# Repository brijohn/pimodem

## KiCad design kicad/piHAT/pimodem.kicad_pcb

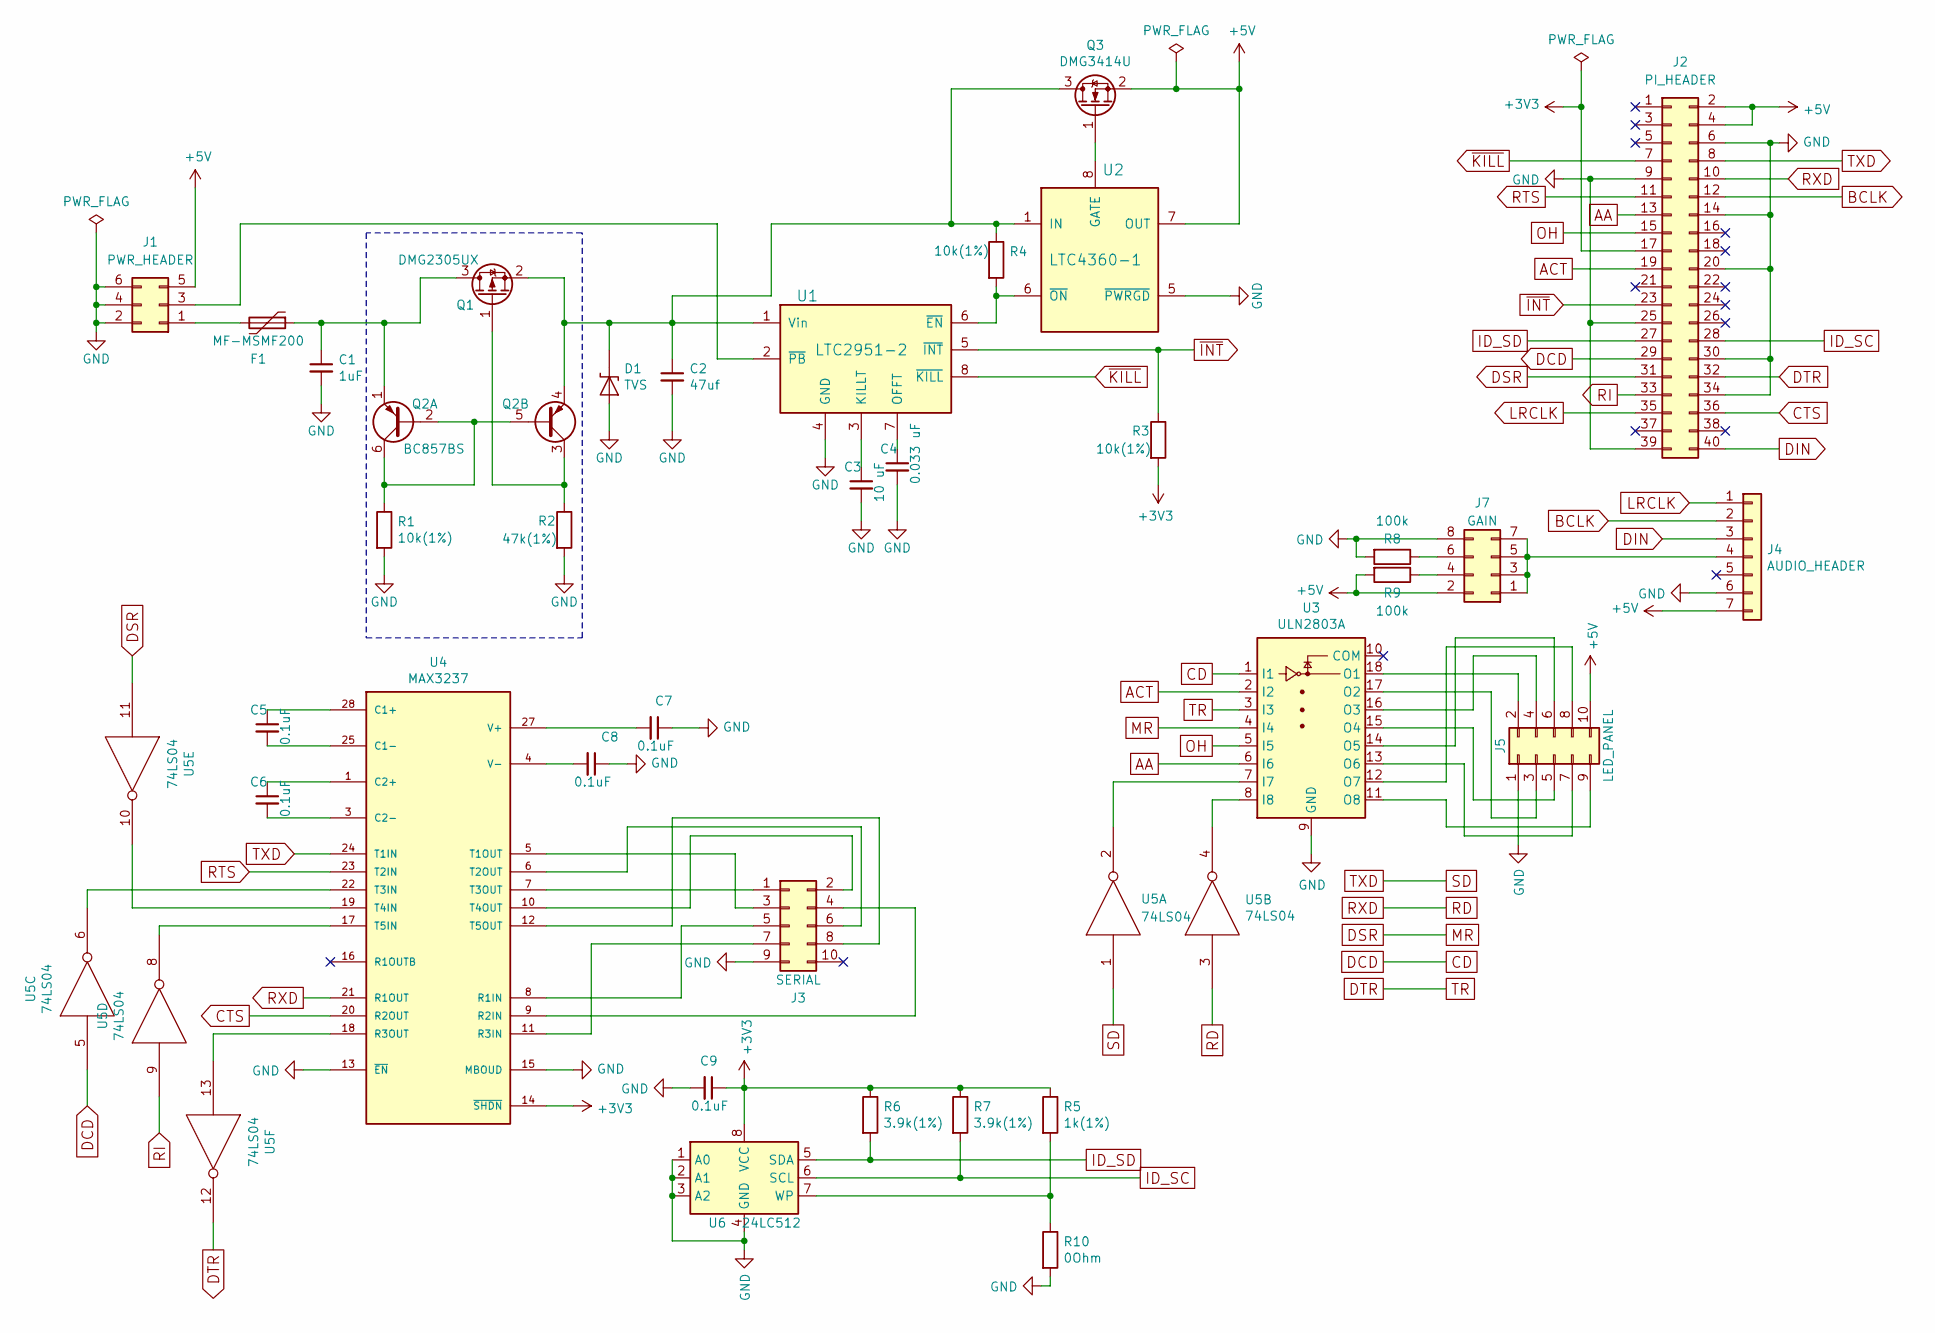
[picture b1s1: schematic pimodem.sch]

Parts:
C1: 1uF; C_0805_2012Metric; Digikey 478-1405-1-ND
C2: 47uf; C_0805_2012Metric; Digikey 445-8239-1-ND
C3: 10 uF; C_0805_2012Metric; Digikey 399-4925-1-ND
C4: 0.033 uF; C_0805_2012Metric; Digikey 732-8024-1-ND
C5: 0.1uF; C_0805_2012Metric; Digikey 399-7999-1-ND
C6, C7, C8, C9: 0.1uF; C_0805_2012Metric
D1: TVS; D_SMB; Digikey SMBJ5.0ALFCT-ND
F1: MF-MSMF200; R_1812_4532Metric; Digikey MF-MSMF200-2CT-ND
J1: PWR_HEADER; Molex_Micro-Fit_3.0_43045-0612_2x03_P3.00mm_Vertical; Digikey WM10679-ND
J2: PI_HEADER; PinSocket_2x20_P2.54mm_Vertical; Digikey S9200-ND
J3: SERIAL; PinHeader_2x05_P2.54mm_Vertical; Digikey 609-3243-ND
J4: AUDIO_HEADER; MAX98357_I2S_DAC; Digikey A31117-ND
J5: LED_PANEL; PinHeader_2x05_P2.54mm_Vertical; Digikey 609-3243-ND
J7: GAIN; PinHeader_2x04_P2.54mm_Vertical; Digikey 609-3391-ND
Q1: DMG2305UX; SOT-23; Digikey DMG2305UX-13DICT-ND
Q2: BC857BS; SOT-363_SC-70-6; Digikey BC857BS-7FDICT-ND
Q3: DMG3414U; SOT-23; Digikey DMG3414U-7DICT-ND
R1: 10k(1%); R_0805_2012Metric; Digikey 311-10.0KCRCT-ND
R2: 47k(1%); R_0805_2012Metric; Digikey 311-47.0KCRCT-ND
R3, R4: 10k(1%); R_0805_2012Metric
R5: 1k(1%); R_0805_2012Metric; Digikey 311-1.00KCRCT-ND
R6: 3.9k(1%); R_0805_2012Metric; Digikey RMCF0805FT3K90CT-ND
R7: 3.9k(1%); R_0805_2012Metric
R8: 100k; R_0805_2012Metric; Digikey 311-100KCRCT-ND
R9: 100k; R_0805_2012Metric
R10: 0Ohm; R_0805_2012Metric; Digikey 311-0.0ARCT-ND
U1: LTC2951-2; SOT-23-8; Digikey LTC2951CTS8-2#TRMPBFCT-ND
U2: LTC4360-1; SC-70-8; Digikey LTC4360ISC8-1#TRMPBFCT-ND
U3: ULN2803A; SOIC-18W_7.5x11.6mm_P1.27mm; Digikey 296-15777-1-ND
U4: MAX3237; SSOP-28_5.3x10.2mm_P0.65mm; Digikey MAX3237EAI+-ND
U5: 74LS04; SOIC-14_3.9x8.7mm_P1.27mm; Digikey 296-14875-1-ND
U6: 24LC512; SOIC-8_3.9x4.9mm_P1.27mm; Digikey CAT24C512WI-GT3OSCT-ND

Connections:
+3V3: C9.1, J2.17, R3.2, R5.1, R6.1, R7.1, U4.14 (~SHDN~), U4.26 (+3V3), U6.8 (VCC)
+5V: J1.5, J2.2, J2.4, J4.7, J5.10, J7.2, Q3.2 (S), R9.2, U2.7 (OUT), U5.14 (+5V)
AA: J2.13, U3.6 (I6)
ACT: J2.19, U3.2 (I2)
BCLK: J2.12, J4.2
CD: J2.29, U3.1 (I1), U5.5
CTS: J2.36, U4.20 (R2OUT)
DIN: J2.40, J4.3
DSR: J2.31, U3.4 (I4), U5.11
DTR: J2.32, U3.3 (I3), U5.12
GND: C1.2, C2.2, C3.2, C4.2, C7.1, C8.1, C9.2, D1.2 (A2), J1.2, J1.4, J1.6, J2.6, J2.9, J2.14, J2.20, J2.25, J2.30, J2.34, J2.39, J3.9, J4.6, J5.1, J7.8, R1.2, R2.2, R8.2, R10.2, U1.4 (GND), U2.2 (GND), U2.3 (GND), U2.4 (GND), U2.5 (~PWRGD~), U3.9 (GND), U4.2 (GND), U4.13 (~EN~), U4.15 (MBOUD), U5.7 (GND), U6.1 (A0), U6.2 (A1), U6.3 (A2), U6.4 (GND)
ID_SC: J2.28, R7.2, U6.6 (SCL)
ID_SD: J2.27, R6.2, U6.5 (SDA)
LRCLK: J2.35, J4.1
unnamed: C1.1, F1.1, Q1.3 (D), Q2.1 (E1)
unnamed: C2.1, D1.1 (A1), Q1.2 (S), Q2.4 (E2), Q3.3 (D), R4.1, U1.1 (Vin), U2.1 (IN)
unnamed: C3.1, U1.3 (KILLT)
unnamed: C4.1, U1.7 (OFFT)
unnamed: C5.1, U4.28 (C1+)
unnamed: C5.2, U4.25 (C1-)
unnamed: C6.1, U4.1 (C2+)
unnamed: C6.2, U4.3 (C2-)
unnamed: C7.2, U4.27 (V+)
unnamed: C8.2, U4.4 (V-)
unnamed: F1.2, J1.1
unnamed: J1.3, U1.2 (~PB~)
unnamed: J3.1, U4.7 (T3OUT)
unnamed: J3.2, U4.10 (T4OUT)
unnamed: J3.3, U4.5 (T1OUT)
unnamed: J3.4, U4.9 (R2IN)
unnamed: J3.5, U4.8 (R1IN)
unnamed: J3.6, U4.6 (T2OUT)
unnamed: J3.7, U4.11 (R3IN)
unnamed: J3.8, U4.12 (T5OUT)
unnamed: J4.4, J7.1, J7.3, J7.5, J7.7
unnamed: J5.2, U3.18 (O1)
unnamed: J5.3, U3.17 (O2)
unnamed: J5.4, U3.16 (O3)
unnamed: J5.5, U3.15 (O4)
unnamed: J5.6, U3.14 (O5)
unnamed: J5.7, U3.13 (O6)
unnamed: J5.8, U3.12 (O7)
unnamed: J5.9, U3.11 (O8)
unnamed: J7.4, R9.1
unnamed: J7.6, R8.1
unnamed: Q1.1 (G), Q2.3 (C2), R2.1
unnamed: Q2.2 (B1), Q2.5 (B2), Q2.6 (C1), R1.1
unnamed: Q3.1 (G), U2.8 (GATE)
unnamed: R4.2, U1.6 (~EN~), U2.6 (~ON~)
unnamed: R5.2, R10.1, U6.7 (WP)
unnamed: U3.7 (I7), U5.2
unnamed: U3.8 (I8), U5.4
unnamed: U4.17 (T5IN), U5.8
unnamed: U4.18 (R3OUT), U5.13
unnamed: U4.19 (T4IN), U5.10
unnamed: U4.22 (T3IN), U5.6
OH: J2.15, U3.5 (I5)
RD: J2.10, U4.21 (R1OUT), U5.3
RI: J2.33, U5.9
RTS: J2.11, U4.23 (T2IN)
SD: J2.8, U4.24 (T1IN), U5.1
~INT~: J2.23, R3.1, U1.5 (~INT~)
~KILL~: J2.7, U1.8 (~KILL~)

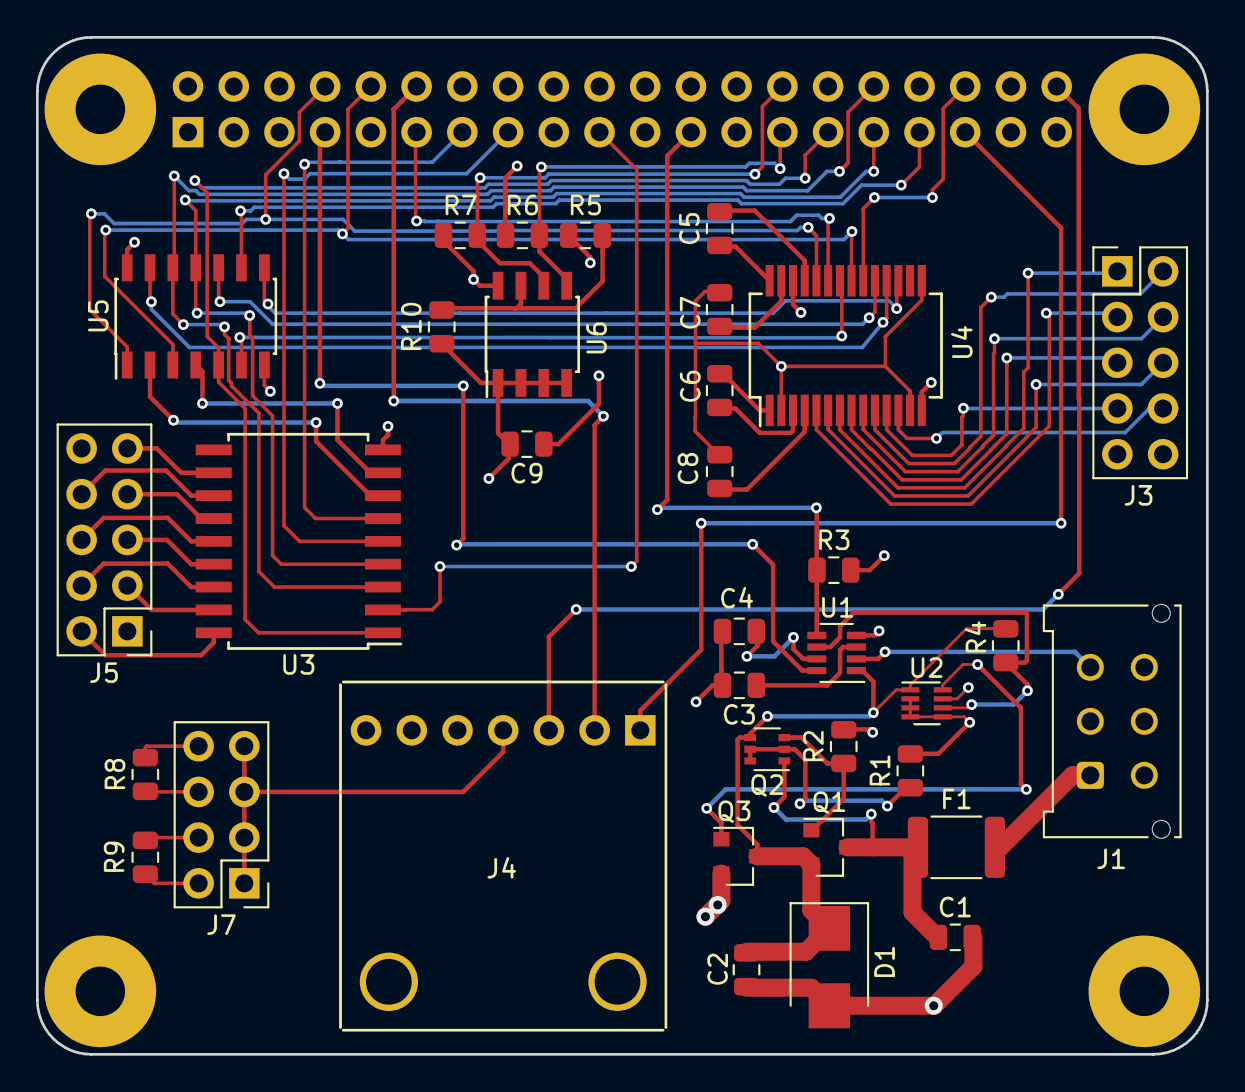
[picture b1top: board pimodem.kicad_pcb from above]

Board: 4 copper layers, 65.0 x 56.5 mm, 36 parts (1 on the bottom side), 63 nets.

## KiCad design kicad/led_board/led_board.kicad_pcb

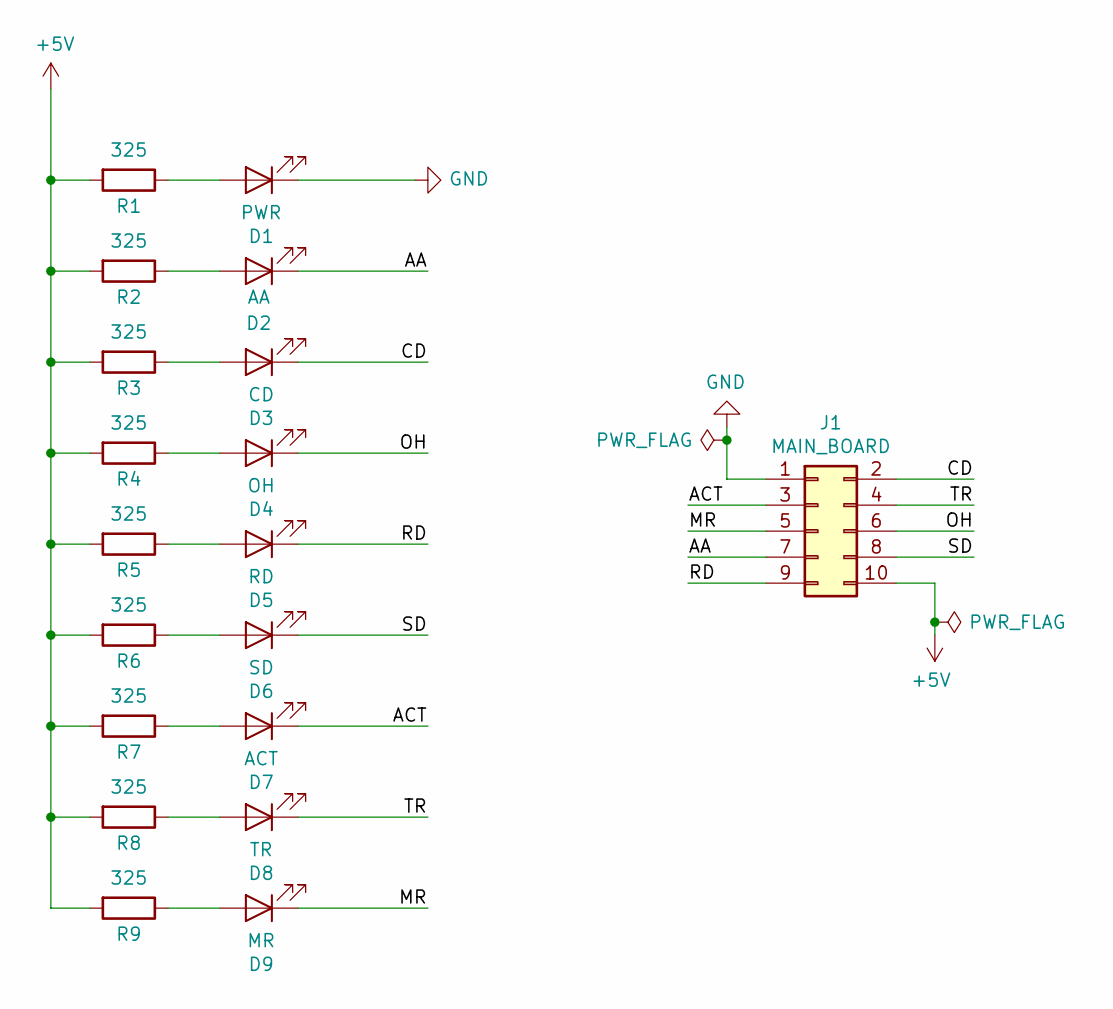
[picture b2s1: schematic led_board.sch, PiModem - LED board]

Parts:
D1: PWR; LED_D5.0mm
D2: AA; LED_D5.0mm
D3: CD; LED_D5.0mm
D4: OH; LED_D5.0mm
D5: RD; LED_D5.0mm
D6: SD; LED_D5.0mm
D7: ACT; LED_D5.0mm
D8: TR; LED_D5.0mm
D9: MR; LED_D5.0mm
J1: MAIN_BOARD; PinHeader_2x05_P2.54mm_Vertical
R1, R2, R3, R4, R5, R6, R7, R8, R9: 325; R_Axial_DIN0207_L6.3mm_D2.5mm_P10.16mm_Horizontal

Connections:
+5V: J1.10, R1.2, R2.2, R3.2, R4.2, R5.2, R6.2, R7.2, R8.2, R9.2
/AA: D2.1 (K), J1.7
/ACT: D7.1 (K), J1.3
/CD: D3.1 (K), J1.2
/MR: D9.1 (K), J1.5
/OH: D4.1 (K), J1.6
/RD: D5.1 (K), J1.9
/SD: D6.1 (K), J1.8
/TR: D8.1 (K), J1.4
GND: D1.1 (K), J1.1
unnamed: D1.2 (A), R1.1
unnamed: D2.2 (A), R2.1
unnamed: D3.2 (A), R3.1
unnamed: D4.2 (A), R4.1
unnamed: D5.2 (A), R5.1
unnamed: D6.2 (A), R6.1
unnamed: D7.2 (A), R7.1
unnamed: D8.2 (A), R8.1
unnamed: D9.2 (A), R9.1

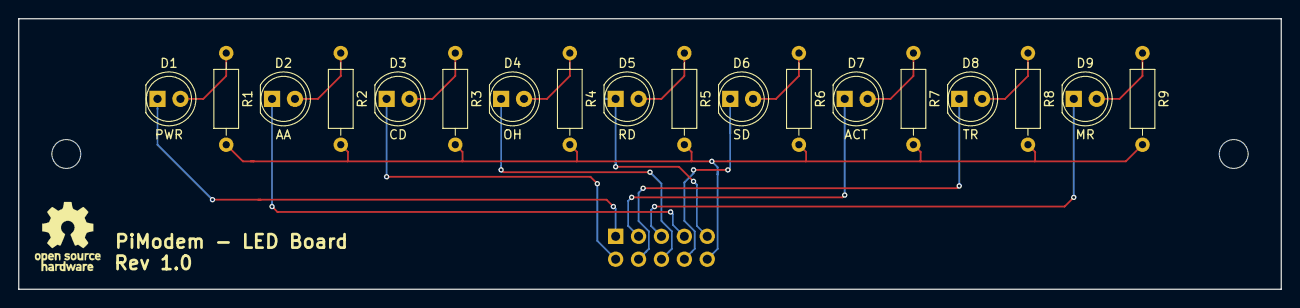
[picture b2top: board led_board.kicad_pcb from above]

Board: 2 copper layers, 140.0 x 30.0 mm, 19 parts (1 on the bottom side), 19 nets.

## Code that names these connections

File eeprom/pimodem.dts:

// Definitions for PiModem HAT
/dts-v1/;
/plugin/;

/ {
	compatible = "brcm,bcm2708";

	fragment@0 {
		target = <&i2s>;
		__overlay__ {
			status = "okay";
		};
	};

	fragment@1 {
		target-path = "/";
		__overlay__ {
			pcm5102a-codec {
				#sound-dai-cells = <0>;
				compatible = "ti,pcm5102a";
				status = "okay";
			};
		};
	};

	fragment@2 {
		target = <&sound>;
		__overlay__ {
			compatible = "hifiberry,hifiberry-dac";
			i2s-controller = <&i2s>;
			status = "okay";
		};
	};

	fragment@3 {
		target = <&uart0>;
		__overlay__ {
			pinctrl-names = "default";
			pinctrl-0 = <&uart0_pins>;
			status = "okay";
		};
	};

	fragment@4 {
		target = <&gpio>;
		__overlay__ {
			uart0_pins: uart0_pins {
				brcm,pins = <14 15 16 17>; /* UART0: TX,RX,CTS,RTS */
				brcm,function = <4 4 7 7>;
				brcm,pull = <0 2 0 0>;
			};
		};
	};

	fragment@5 {
		target-path = "/";
		__overlay__ {
			power_ctrl: power_ctrl {
				compatible = "gpio-poweroff";
				gpios = <&gpio 4 1>;
				force;
			};
		};
	};

	fragment@6 {
		target = <&gpio>;
		__overlay__ {
			power_ctrl_pins: power_ctrl_pins {
				brcm,pins = <4>;
				brcm,function = <1>; // out
			};
		};
	};

	fragment@7 {
		target-path = "/";
		__overlay__ {
			i2c_gpio: i2c@0 {
				compatible = "i2c-gpio";
				gpios = <&gpio 0 0 /* sda */
					 &gpio 1 0 /* scl */
					>;
				i2c-gpio,delay-us = <2>;        /* ~100 kHz */
				#address-cells = <1>;
				#size-cells = <0>;
				at24: at24@50 {
					compatible = "atmel,24c512";
					reg = <0x50>;
				};
			};
		};
	};

	fragment@8 {
		target-path = "/aliases";
		__overlay__ {
			i2c_gpio = "/i2c@0";
		};
	};

	fragment@9 {
		target-path = "/__symbols__";
		__overlay__ {
			i2c_gpio = "/i2c@0";
		};
	};

	fragment@10 {
		target = <&act_led>;
		__overlay__ {
			label = "network:act";
			linux,default-trigger = "none";
			gpios = <&gpio 10 0>;
		};
	};
};

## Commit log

2017-09-06 Add kicad schematic and pcb files
2018-06-17 Update kicad schematic to latest version of kicad nightly
2018-06-18 Add eeprom source
2018-06-18 small update to kicad custom parts
2018-07-04 Add src for pipodem
2018-07-04 Add logging support w/ zerolog
2018-07-04 Add support for ATH1
2018-07-04 Add timeout to dial and return NoAnswer if dial fails
2018-07-04 Busy() now returns true if the line is ringing or a connection is established
2018-07-04 Don't return NoCarrier if connection was hungup locally
2018-07-04 ATA will only pickup phone if it is ringing
2018-07-15 Add support fo register S22
    * Volume
    * Speaker Control
    * Extended Results
2018-07-15 Fix escape sequance detection
2018-07-15 Add top level makefile
2018-07-15 Add .gitignore
2018-09-01 Add gpio hw support
2019-05-18 Update traces for serial header to use DTK/intel format
2019-05-20 Add ability to cross compile pimodem
2019-05-29 Fix eeprom Makefile
2019-06-10 Issue halt syscall when shutdown pin is pulled low
2019-06-15 Add i2c driver to device tree eeprom blob
2019-06-15 eeprom: Add shutdown pin to pins.yaml
2019-06-15 eeprom: add nvmem layout file
2019-06-15 kicad: update schematic to use 128kbit eeprom
2019-06-17 gitignore: add Gopkg.lock
2019-06-20 eeprom: add network activity LED
2019-06-20 eeprom: add netmask and gateway to nvmem.yaml
2019-06-20 build: add rpi build tag to makefile
2019-06-20 pimodem: add support for DTR signal
2019-06-20 pimodem: add ATI command
2020-04-04 pimodem: Update ATI to list all interfaces (eth or wlan)
2020-04-04 pimodem: Fix DTR triggered when asserted
2020-04-04 pimodem: change name of audio file played when connecting
2020-04-05 pimodem: handle all line responses in the main loop
2020-04-05 pimodem: add DCD handler
2020-04-05 kicad: Update schematic and pcb layout
    * Connect serial gpio signals through inverter gates
    * Connect all leds to gpio pins
    * Update eeprom to 24c512
    * Update pcb footprints to new names (kicad update)
    * Update schematic/board revision to 1.2
2020-04-05 build: update .gitignore
2020-04-05 eeprom: update to 64kb eeprom
2020-04-06 pimodem: Set syslog facility to local7
2020-04-06 pimodem: Always send NoCarrier when getting a tcp read error
2020-04-07 eeprom: minor update to nvmem.yaml
2020-04-11 pimodem: Add support for storing and loading profiles from nvmem
2020-04-12 eeprom: expand eeprom to include default settings for new install
2020-04-13 eeprom: Add 'aa' and 'oh' pins to eeprom config
2020-04-14 pimodem: add on write callbacks to registers (use for setting dcd led status)
2020-04-14 pimodem: Add support for DSR rs232 signal
2020-04-16 pimodem: Add 'AA' led support
2020-12-03 kicad: Add LED front panel board
2020-12-04 pimodem: Add GPL2 license
2020-12-14 kicad: add copyright and license to kicad documents

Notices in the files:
kicad/led_board/led_board.kicad_pcb:
License: GPLv2
Copyright (c) 2019-2020
kicad/piHAT/pimodem.kicad_pcb:
Copyright (c) 2017-2020
